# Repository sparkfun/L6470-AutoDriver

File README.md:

SparkFun AutoDriver - Stepper Motor Driver
==========================================

[*AutoDriver (BOB-13752)*](https://www.sparkfun.com/products/13752)

The AutoDriver is a bipolar stepper driver based on the ST Micro L6470 chip. It allows a processor to control a single 3A bipolar stepper motor across an 8-45V supply range.

Repository Contents
-------------------
* **/Hardware** - All Eagle design files (.brd, .sch)
* **/Libraries** - All Arduino libraries and board examples
* **/Production** - Test bed files and production panel files

Documentation
--------------
* **[Library](https://github.com/sparkfun/SparkFun_AutoDriver_Arduino_Library)** - Arduino library for the AutoDriver.
* **[Hookup Guide](https://learn.sparkfun.com/tutorials/getting-started-with-the-autodriver---v13)** - Basic hookup guide for the Auto Driver.
* **[SparkFun Fritzing repo](https://github.com/sparkfun/Fritzing_Parts)** - Fritzing diagrams for SparkFun products.
* **[SparkFun 3D Model repo](https://github.com/sparkfun/3D_Models)** - 3D models of SparkFun products. 
* **[SparkFun Graphical Datasheets](https://github.com/sparkfun/Graphical_Datasheets)** -Graphical Datasheets for various SparkFun products.

License Information
-------------------

This product is _**open source**_! 

Please review the LICENSE.md file for license information. 

If you have any questions or concerns on licensing, please contact techsupport@sparkfun.com.

Distributed as-is; no warranty is given.

- Your friends at SparkFun.

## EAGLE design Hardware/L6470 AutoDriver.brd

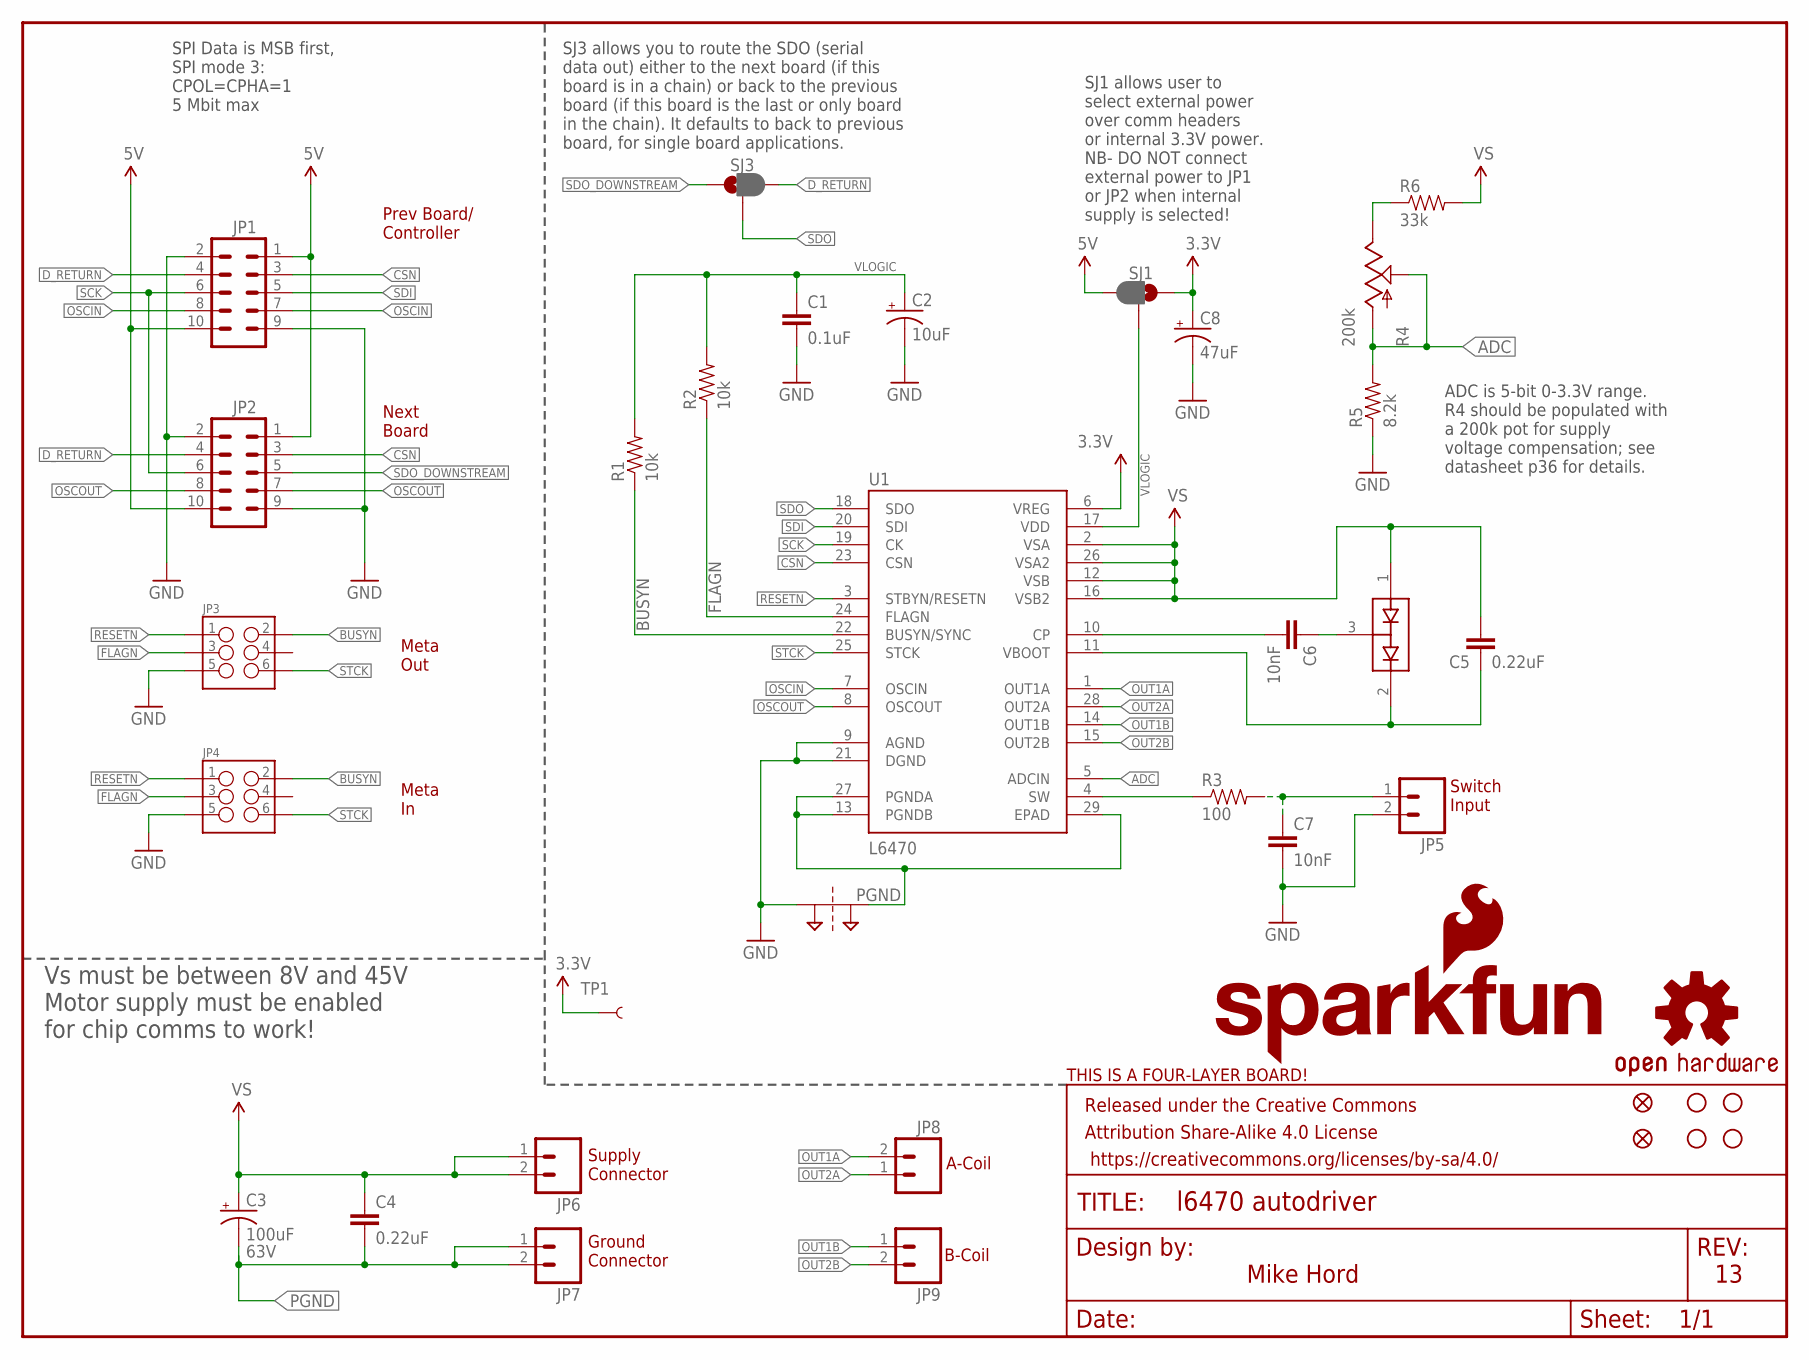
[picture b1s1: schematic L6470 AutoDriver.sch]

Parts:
C1: 0.1uF; 0603-CAP
C2: 10uF; EIA3216
C3: 100uF; NIC_10X10.5_CAP
C4, C5: 0.22uF; 0603-CAP
C6, C7: 10nF; 0603-CAP
C8: 47uF; EIA3528
D1: BAV99; SOT23-3
FID1, FID2: FIDUCIALUFIDUCIAL; MICRO-FIDUCIAL
FRAME1: FRAME-LETTER; CREATIVE_COMMONS
JP1, JP2: M05X2SHD; 2X5-SHROUDED
JP3, JP4: M03X2SHROUD; 2X3-SHROUDED
JP5, JP6, JP7, JP8, JP9: M023.5MM; SCREWTERMINAL-3.5MM-2
LOGO1: OSHW-LOGOM; OSHW-LOGO-M
LOGO2: SFE_LOGO_NAME_FLAME.2_INCH; SFE_LOGO_NAME_FLAME_.2
R1, R2: 10k; 0603-RES
R3: 100; 0603-RES
R4: 200k; 3362U
R5: 8.2k; 0603-RES
R6: 33k; 0603-RES
SJ1, SJ3: JUMPER-PAD-3-2OF3_NC_BY_PASTE; PAD-JUMPER-3-2OF3_NC_BY_PASTE_YES_SILK_FULL_BOX
SJ2: 2PT_GND_TIE
STANDOFF1, STANDOFF2, STANDOFF3, STANDOFF4: STAND-OFF
TP1: TEST-POINTTP_15TH_THRU; TP_15TH
U1: L6470; HTSSOP28
U$4: FOUR_LAYER_WARNING

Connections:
3.3V: C8.A (+), SJ1.1, TP1.P$1, U1.6 (VREG)
5V: JP1.1, JP1.10, JP2.1, JP2.10, SJ1.3
ADC: R4.P$2 (S), R4.P$3 (A), R5.2, U1.5 (ADCIN)
BUSYN: JP3.2, JP4.2, R1.1, U1.22 (BUSYN/SYNC)
CP_HIGH: C6.1, D1.3 (COM)
CSN: JP1.3, JP2.3, U1.23 (CSN)
D_RETURN: JP1.4, JP2.4, SJ3.3
FLAGN: JP3.3, JP4.3, R2.1, U1.24 (FLAGN)
GND: C1.2, C2.C (-), C7.2, C8.C (-), JP1.2, JP1.9, JP2.2, JP2.9, JP3.5, JP4.5, JP5.2, R5.1, SJ2.P$1, U1.9 (AGND), U1.21 (DGND)
unnamed: R4.P$1 (E), R6.1
OSCIN: JP1.7, JP1.8, U1.7 (OSCIN)
OSCOUT: JP2.7, JP2.8, U1.8 (OSCOUT)
OUT1A: JP8.2, U1.1 (OUT1A)
OUT1B: JP9.1, U1.14 (OUT1B)
OUT2A: JP8.1, U1.28 (OUT2A)
OUT2B: JP9.2, U1.15 (OUT2B)
PGND: C3.-, C4.2, JP7.1, JP7.2, SJ2.P$2, U1.13 (PGNDB), U1.27 (PGNDA), U1.29 (EPAD)
RESETN: JP3.1, JP4.1, U1.3 (STBYN/RESETN)
SCK: JP1.6, JP2.6, U1.19 (CK)
SDI: JP1.5, U1.20 (SDI)
SDO: SJ3.2, U1.18 (SDO)
SDO_DOWNSTREAM: JP2.5, SJ3.1
STCK: JP3.6, JP4.6, U1.25 (STCK)
SWITCH_INPUT: C7.1, JP5.1, R3.2
SWITCH_SIG: R3.1, U1.4 (SW)
VLOGIC: C1.1, C2.A (+), R1.2, R2.2, SJ1.2, U1.17 (VDD)
VS: C3.+, C4.1, C5.2, D1.1 (A1), JP6.1, JP6.2, R6.2, U1.2 (VSA), U1.12 (VSB), U1.16 (VSB2), U1.26 (VSA2)
V_BOOT: C5.1, D1.2 (C2), U1.11 (VBOOT)
V_CP: C6.2, U1.10 (CP)

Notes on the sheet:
63V
Switch Input
B-Coil
A-Coil
Supply Connector
Ground Connector
SJ1 allows user to select external power over comm headers or internal 3.3V power. NB- DO NOT connect external power to JP1 or JP2 when internal supply is selected!
Next Board
Prev Board/ Controller
Meta Out
Meta In
ADC is 5-bit 0-3.3V range. R4 should be populated with a 200k pot for supply voltage compensation; see datasheet p36 for details.
SPI Data is MSB first, SPI mode 3: CPOL=CPHA=1 5 Mbit max
Mike Hord
Vs must be between 8V and 45V Motor supply must be enabled for chip comms to work!
SJ3 allows you to route the SDO (serial data out) either to the next board (if this board is in a chain) or back to the previous board (if this board is the last or only board in the chain). It defaults to back to previous board, for single board applications.

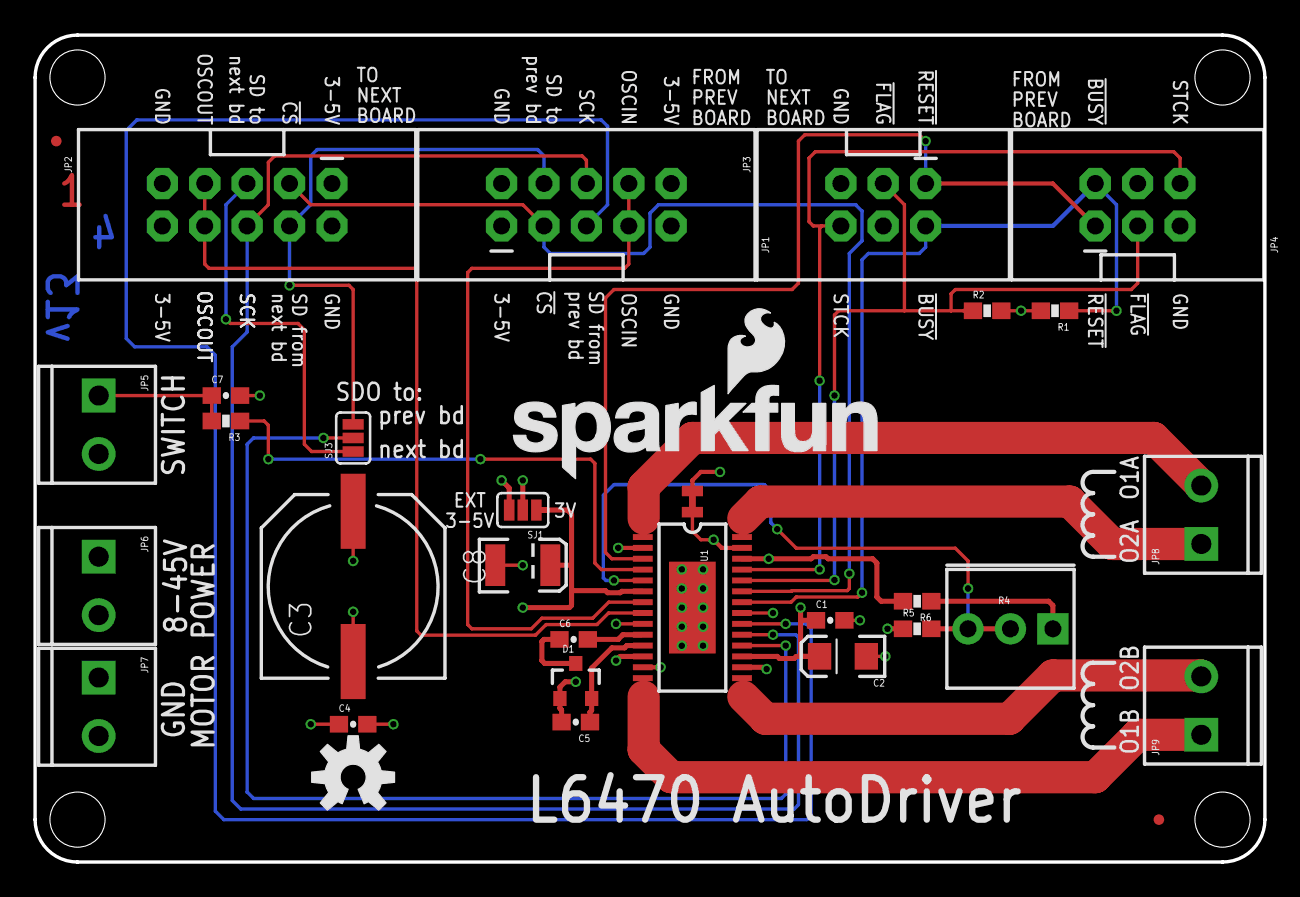
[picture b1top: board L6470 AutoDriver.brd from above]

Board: 4 copper layers, 73.7 x 49.5 mm, 39 parts (0 on the bottom side), 29 nets.

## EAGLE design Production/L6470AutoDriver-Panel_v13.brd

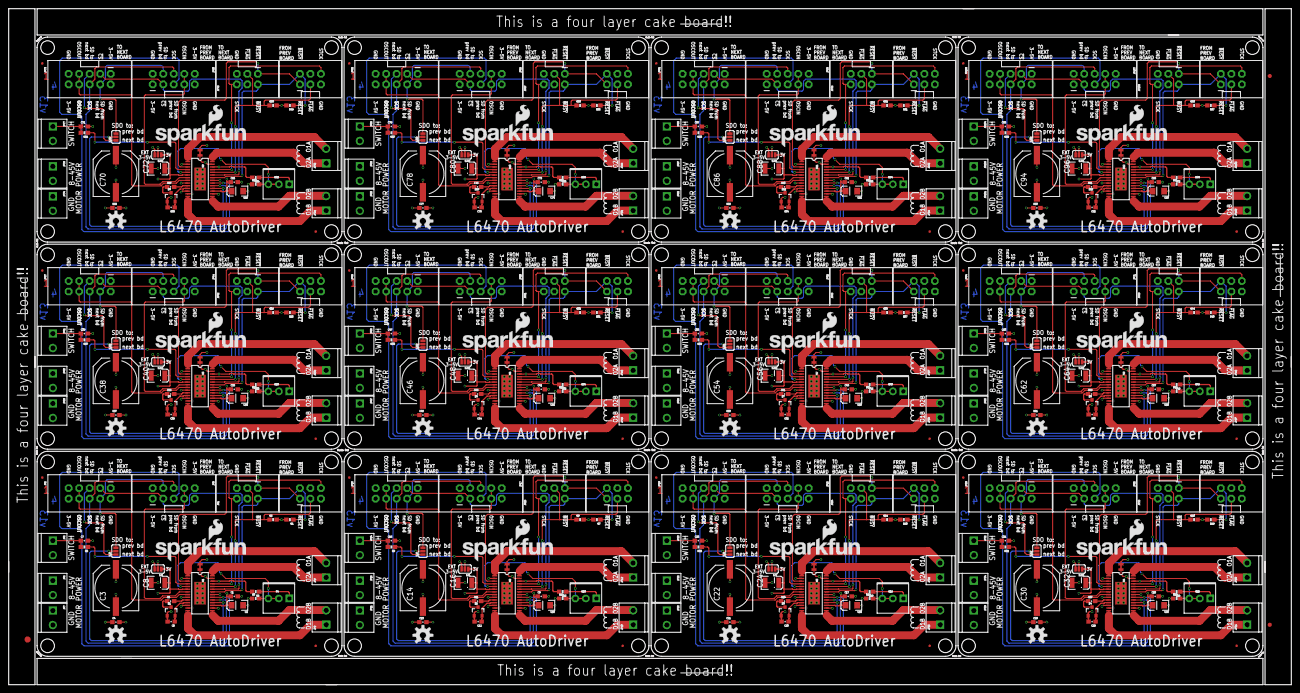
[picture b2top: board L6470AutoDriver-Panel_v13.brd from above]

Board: 4 copper layers, 309.9 x 163.3 mm, 447 parts (0 on the bottom side), 348 nets.

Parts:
C1, C9, C17, C25, C33, C41, C49, C57, C65, C73, C81, C89: 0.1uF; 0603-CAP
C2, C10, C18, C26, C34, C42, C50, C58, C66, C74, C82, C90: 10uF; EIA3216
C3, C14, C22, C30, C38, C46, C54, C62, C70, C78, C86, C94: 100uF; NIC_10X10.5_CAP
C4, C5, C12, C13, C20, C21, C28, C29, C36, C37, C44, C45, C52, C53, C60, C61, C68, C69, C76, C77, C84, C85, C92, C93: 0.22uF; 0603-CAP
C6, C7, C11, C15, C19, C23, C27, C31, C35, C39, C43, C47, C51, C55, C59, C63, C67, C71, C75, C79, C83, C87, C91, C95: 10nF; 0603-CAP
C8, C16, C24, C32, C40, C48, C56, C64, C72, C80, C88, C96: 47uF; EIA3528
D1, D2, D3, D4, D5, D6, D7, D8, D9, D10, D11, D12: BAV99; SOT23-3
E$1: FIDUCIAL-1.5X3
E$5, E$6: FIDUCIAL-1X2
FID1, FID2, FID3, FID4, FID5, FID6, FID7, FID8, FID9, FID10, FID11, FID12, FID13, FID14, FID15, FID16, FID17, FID18, FID19, FID20, FID21, FID22, FID23, FID24: FIDUCIALUFIDUCIAL; MICRO-FIDUCIAL
JP1, JP2, JP10, JP15, JP19, JP24, JP28, JP33, JP37, JP42, JP46, JP51, JP55, JP60, JP64, JP69, JP73, JP78, JP82, JP87, JP91, JP96, JP100, JP105: M05X2SHD; 2X5-SHROUDED
JP3, JP4, JP17, JP18, JP26, JP27, JP35, JP36, JP44, JP45, JP53, JP54, JP62, JP63, JP71, JP72, JP80, JP81, JP89, JP90, JP98, JP99, JP107, JP108: 2X3-SHROUDED
JP5, JP6, JP7, JP8, JP9, JP11, JP12, JP13, JP14, JP16, JP20, JP21, JP22, JP23, JP25, JP29, JP30, JP31, JP32, JP34, JP38, JP39, JP40, JP41, JP43, JP47, JP48, JP49, JP50, JP52, JP56, JP57, JP58, JP59, JP61, JP65, JP66, JP67, JP68, JP70, JP74, JP75, JP76, JP77, JP79, JP83, JP84, JP85, JP86, JP88, JP92, JP93, JP94, JP95, JP97, JP101, JP102, JP103, JP104, JP106: SCREWTERMINAL-3.5MM-2
LOGO1, LOGO3, LOGO5, LOGO7, LOGO9, LOGO11, LOGO13, LOGO15, LOGO17, LOGO19, LOGO21, LOGO23: OSHW-LOGOM; OSHW-LOGO-M
LOGO2, LOGO4, LOGO6, LOGO8, LOGO10, LOGO12, LOGO14, LOGO16, LOGO18, LOGO20, LOGO22, LOGO24: SFE_LOGO_NAME_FLAME.2_INCH; SFE_LOGO_NAME_FLAME_.2
R1, R2, R7, R8, R13, R14, R19, R20, R25, R26, R31, R32, R37, R38, R43, R44, R49, R50, R55, R56, R61, R62, R67, R68: 10k; 0603-RES
R3, R9, R15, R21, R27, R33, R39, R45, R51, R57, R63, R69: 100; 0603-RES
R4, R10, R16, R22, R28, R34, R40, R46, R52, R58, R64, R70: 200k; 3362U
R5, R11, R17, R23, R29, R35, R41, R47, R53, R59, R65, R71: 8.2k; 0603-RES
R6, R12, R18, R24, R30, R36, R42, R48, R54, R60, R66, R72: 33k; 0603-RES
SJ1, SJ3, SJ4, SJ6, SJ7, SJ9, SJ10, SJ12, SJ13, SJ15, SJ16, SJ18, SJ19, SJ21, SJ22, SJ24, SJ25, SJ27, SJ28, SJ30, SJ31, SJ33, SJ34, SJ36: JUMPER-PAD-3-2OF3_NC_BY_PASTE; PAD-JUMPER-3-2OF3_NC_BY_PASTE_YES_SILK_FULL_BOX
SJ2, SJ5, SJ8, SJ11, SJ14, SJ17, SJ20, SJ23, SJ26, SJ29, SJ32, SJ35: 2PT_GND_TIE
STANDOFF1, STANDOFF2, STANDOFF3, STANDOFF4, STANDOFF5, STANDOFF6, STANDOFF7, STANDOFF8, STANDOFF9, STANDOFF10, STANDOFF11, STANDOFF12, STANDOFF13, STANDOFF14, STANDOFF15, STANDOFF16, STANDOFF17, STANDOFF18, STANDOFF19, STANDOFF20, STANDOFF21, STANDOFF22, STANDOFF23, STANDOFF24, STANDOFF25, STANDOFF26, STANDOFF27, STANDOFF28, STANDOFF29, STANDOFF30, STANDOFF31, STANDOFF32, STANDOFF33, STANDOFF34, STANDOFF35, STANDOFF36, STANDOFF37, STANDOFF38, STANDOFF39, STANDOFF40, STANDOFF41, STANDOFF42, STANDOFF43, STANDOFF44, STANDOFF45, STANDOFF46, STANDOFF47, STANDOFF48: STAND-OFF
TP1, TP2, TP3, TP4, TP5, TP6, TP7, TP8, TP9, TP10, TP11, TP12: TEST-POINTTP_15TH_THRU; TP_15TH
U1, U2, U3, U4, U5, U6, U7, U8, U9, U10, U11, U12: L6470; HTSSOP28

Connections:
3.3V: C8.A, SJ1.1, TP1.P$1, U1.6
3.3V1: C16.A, SJ4.1, TP2.P$1, U2.6
3.3V2: C24.A, SJ7.1, TP3.P$1, U3.6
3.3V3: C32.A, SJ10.1, TP4.P$1, U4.6
3.3V4: C40.A, SJ13.1, TP5.P$1, U5.6
3.3V5: C48.A, SJ16.1, TP6.P$1, U6.6
3.3V6: C56.A, SJ19.1, TP7.P$1, U7.6
3.3V7: C64.A, SJ22.1, TP8.P$1, U8.6
3.3V8: C72.A, SJ25.1, TP9.P$1, U9.6
3.3V9: C80.A, SJ28.1, TP10.P$1, U10.6
3.3V10: C88.A, SJ31.1, TP11.P$1, U11.6
3.3V11: C96.A, SJ34.1, TP12.P$1, U12.6
5V: JP1.1, JP1.10, JP2.1, JP2.10, SJ1.3
5V1: JP10.1, JP10.10, JP15.1, JP15.10, SJ4.3
5V2: JP19.1, JP19.10, JP24.1, JP24.10, SJ7.3
5V3: JP28.1, JP28.10, JP33.1, JP33.10, SJ10.3
5V4: JP37.1, JP37.10, JP42.1, JP42.10, SJ13.3
5V5: JP46.1, JP46.10, JP51.1, JP51.10, SJ16.3
5V6: JP55.1, JP55.10, JP60.1, JP60.10, SJ19.3
5V7: JP64.1, JP64.10, JP69.1, JP69.10, SJ22.3
5V8: JP73.1, JP73.10, JP78.1, JP78.10, SJ25.3
5V9: JP82.1, JP82.10, JP87.1, JP87.10, SJ28.3
5V10: JP91.1, JP91.10, JP96.1, JP96.10, SJ31.3
5V11: JP100.1, JP100.10, JP105.1, JP105.10, SJ34.3
ADC: R4.P$2, R4.P$3, R5.2, U1.5
ADC1: R10.P$2, R10.P$3, R11.2, U2.5
ADC2: R16.P$2, R16.P$3, R17.2, U3.5
ADC3: R22.P$2, R22.P$3, R23.2, U4.5
ADC4: R28.P$2, R28.P$3, R29.2, U5.5
ADC5: R34.P$2, R34.P$3, R35.2, U6.5
ADC6: R40.P$2, R40.P$3, R41.2, U7.5
ADC7: R46.P$2, R46.P$3, R47.2, U8.5
ADC8: R52.P$2, R52.P$3, R53.2, U9.5
ADC9: R58.P$2, R58.P$3, R59.2, U10.5
ADC10: R64.P$2, R64.P$3, R65.2, U11.5
ADC11: R70.P$2, R70.P$3, R71.2, U12.5
BUSYN: JP3.2, JP4.2, R1.1, U1.22
BUSYN1: JP17.2, JP18.2, R7.1, U2.22
BUSYN2: JP26.2, JP27.2, R13.1, U3.22
BUSYN3: JP35.2, JP36.2, R19.1, U4.22
BUSYN4: JP44.2, JP45.2, R25.1, U5.22
BUSYN5: JP53.2, JP54.2, R31.1, U6.22
BUSYN6: JP62.2, JP63.2, R37.1, U7.22
BUSYN7: JP71.2, JP72.2, R43.1, U8.22
BUSYN8: JP80.2, JP81.2, R49.1, U9.22
BUSYN9: JP89.2, JP90.2, R55.1, U10.22
BUSYN10: JP98.2, JP99.2, R61.1, U11.22
BUSYN11: JP107.2, JP108.2, R67.1, U12.22
CP_HIGH: C6.1, D1.3
CP_HIGH1: C11.1, D2.3
CP_HIGH2: C19.1, D3.3
CP_HIGH3: C27.1, D4.3
CP_HIGH4: C35.1, D5.3
CP_HIGH5: C43.1, D6.3
CP_HIGH6: C51.1, D7.3
CP_HIGH7: C59.1, D8.3
CP_HIGH8: C67.1, D9.3
CP_HIGH9: C75.1, D10.3
CP_HIGH10: C83.1, D11.3
CP_HIGH11: C91.1, D12.3
CSN: JP1.3, JP2.3, U1.23
CSN1: JP10.3, JP15.3, U2.23
CSN2: JP19.3, JP24.3, U3.23
CSN3: JP28.3, JP33.3, U4.23
CSN4: JP37.3, JP42.3, U5.23
CSN5: JP46.3, JP51.3, U6.23
CSN6: JP55.3, JP60.3, U7.23
CSN7: JP64.3, JP69.3, U8.23
CSN8: JP73.3, JP78.3, U9.23
CSN9: JP82.3, JP87.3, U10.23
CSN10: JP91.3, JP96.3, U11.23
CSN11: JP100.3, JP105.3, U12.23
D_RETURN: JP1.4, JP2.4, SJ3.3
D_RETURN1: JP10.4, JP15.4, SJ6.3
D_RETURN2: JP19.4, JP24.4, SJ9.3
D_RETURN3: JP28.4, JP33.4, SJ12.3
D_RETURN4: JP37.4, JP42.4, SJ15.3
D_RETURN5: JP46.4, JP51.4, SJ18.3
D_RETURN6: JP55.4, JP60.4, SJ21.3
D_RETURN7: JP64.4, JP69.4, SJ24.3
D_RETURN8: JP73.4, JP78.4, SJ27.3
D_RETURN9: JP82.4, JP87.4, SJ30.3
D_RETURN10: JP91.4, JP96.4, SJ33.3
D_RETURN11: JP100.4, JP105.4, SJ36.3
FLAGN: JP3.3, JP4.3, R2.1, U1.24
FLAGN1: JP17.3, JP18.3, R8.1, U2.24
FLAGN2: JP26.3, JP27.3, R14.1, U3.24
FLAGN3: JP35.3, JP36.3, R20.1, U4.24
FLAGN4: JP44.3, JP45.3, R26.1, U5.24
FLAGN5: JP53.3, JP54.3, R32.1, U6.24
FLAGN6: JP62.3, JP63.3, R38.1, U7.24
FLAGN7: JP71.3, JP72.3, R44.1, U8.24
FLAGN8: JP80.3, JP81.3, R50.1, U9.24
FLAGN9: JP89.3, JP90.3, R56.1, U10.24
FLAGN10: JP98.3, JP99.3, R62.1, U11.24
FLAGN11: JP107.3, JP108.3, R68.1, U12.24
GND: C1.2, C2.C, C7.2, C8.C, JP1.2, JP1.9, JP2.2, JP2.9, JP3.5, JP4.5, JP5.2, R5.1, SJ2.P$1, U1.9, U1.21
GND1: C9.2, C10.C, C15.2, C16.C, JP10.2, JP10.9, JP14.2, JP15.2, JP15.9, JP17.5, JP18.5, R11.1, SJ5.P$1, U2.9, U2.21
GND2: C17.2, C18.C, C23.2, C24.C, JP19.2, JP19.9, JP23.2, JP24.2, JP24.9, JP26.5, JP27.5, R17.1, SJ8.P$1, U3.9, U3.21
GND3: C25.2, C26.C, C31.2, C32.C, JP28.2, JP28.9, JP32.2, JP33.2, JP33.9, JP35.5, JP36.5, R23.1, SJ11.P$1, U4.9, U4.21
GND4: C33.2, C34.C, C39.2, C40.C, JP37.2, JP37.9, JP41.2, JP42.2, JP42.9, JP44.5, JP45.5, R29.1, SJ14.P$1, U5.9, U5.21
GND5: C41.2, C42.C, C47.2, C48.C, JP46.2, JP46.9, JP50.2, JP51.2, JP51.9, JP53.5, JP54.5, R35.1, SJ17.P$1, U6.9, U6.21
GND6: C49.2, C50.C, C55.2, C56.C, JP55.2, JP55.9, JP59.2, JP60.2, JP60.9, JP62.5, JP63.5, R41.1, SJ20.P$1, U7.9, U7.21
GND7: C57.2, C58.C, C63.2, C64.C, JP64.2, JP64.9, JP68.2, JP69.2, JP69.9, JP71.5, JP72.5, R47.1, SJ23.P$1, U8.9, U8.21
GND8: C65.2, C66.C, C71.2, C72.C, JP73.2, JP73.9, JP77.2, JP78.2, JP78.9, JP80.5, JP81.5, R53.1, SJ26.P$1, U9.9, U9.21
GND9: C73.2, C74.C, C79.2, C80.C, JP82.2, JP82.9, JP86.2, JP87.2, JP87.9, JP89.5, JP90.5, R59.1, SJ29.P$1, U10.9, U10.21
GND10: C81.2, C82.C, C87.2, C88.C, JP91.2, JP91.9, JP95.2, JP96.2, JP96.9, JP98.5, JP99.5, R65.1, SJ32.P$1, U11.9, U11.21
GND11: C89.2, C90.C, C95.2, C96.C, JP100.2, JP100.9, JP104.2, JP105.2, JP105.9, JP107.5, JP108.5, R71.1, SJ35.P$1, U12.9, U12.21
unnamed: R10.P$1, R12.1
unnamed: R16.P$1, R18.1
unnamed: R22.P$1, R24.1
unnamed: R28.P$1, R30.1
unnamed: R34.P$1, R36.1
unnamed: R40.P$1, R42.1
unnamed: R46.P$1, R48.1
unnamed: R52.P$1, R54.1
unnamed: R58.P$1, R60.1
unnamed: R64.P$1, R66.1
unnamed: R4.P$1, R6.1
unnamed: R70.P$1, R72.1
OSCIN: JP1.7, JP1.8, U1.7
OSCIN1: JP15.7, JP15.8, U2.7
OSCIN2: JP24.7, JP24.8, U3.7
OSCIN3: JP33.7, JP33.8, U4.7
OSCIN4: JP42.7, JP42.8, U5.7
OSCIN5: JP51.7, JP51.8, U6.7
OSCIN6: JP60.7, JP60.8, U7.7
OSCIN7: JP69.7, JP69.8, U8.7
OSCIN8: JP78.7, JP78.8, U9.7
OSCIN9: JP87.7, JP87.8, U10.7
OSCIN10: JP96.7, JP96.8, U11.7
OSCIN11: JP105.7, JP105.8, U12.7
OSCOUT: JP2.7, JP2.8, U1.8
OSCOUT1: JP10.7, JP10.8, U2.8
OSCOUT2: JP19.7, JP19.8, U3.8
OSCOUT3: JP28.7, JP28.8, U4.8
OSCOUT4: JP37.7, JP37.8, U5.8
OSCOUT5: JP46.7, JP46.8, U6.8
OSCOUT6: JP55.7, JP55.8, U7.8
OSCOUT7: JP64.7, JP64.8, U8.8
OSCOUT8: JP73.7, JP73.8, U9.8
OSCOUT9: JP82.7, JP82.8, U10.8
OSCOUT10: JP91.7, JP91.8, U11.8
OSCOUT11: JP100.7, JP100.8, U12.8
OUT1A: JP8.2, U1.1
OUT1A1: JP12.2, U2.1
OUT1A2: JP21.2, U3.1
OUT1A3: JP30.2, U4.1
OUT1A4: JP39.2, U5.1
OUT1A5: JP48.2, U6.1
OUT1A6: JP57.2, U7.1
OUT1A7: JP66.2, U8.1
OUT1A8: JP75.2, U9.1
OUT1A9: JP84.2, U10.1
OUT1A10: JP93.2, U11.1
OUT1A11: JP102.2, U12.1
OUT1B: JP9.1, U1.14
OUT1B1: JP13.1, U2.14
OUT1B2: JP22.1, U3.14
OUT1B3: JP31.1, U4.14
OUT1B4: JP40.1, U5.14
OUT1B5: JP49.1, U6.14
OUT1B6: JP58.1, U7.14
OUT1B7: JP67.1, U8.14
OUT1B8: JP76.1, U9.14
OUT1B9: JP85.1, U10.14
OUT1B10: JP94.1, U11.14
OUT1B11: JP103.1, U12.14
OUT2A: JP8.1, U1.28
OUT2A1: JP12.1, U2.28
OUT2A2: JP21.1, U3.28
OUT2A3: JP30.1, U4.28
OUT2A4: JP39.1, U5.28
OUT2A5: JP48.1, U6.28
OUT2A6: JP57.1, U7.28
OUT2A7: JP66.1, U8.28
OUT2A8: JP75.1, U9.28
OUT2A9: JP84.1, U10.28
OUT2A10: JP93.1, U11.28
OUT2A11: JP102.1, U12.28
OUT2B: JP9.2, U1.15
OUT2B1: JP13.2, U2.15
OUT2B2: JP22.2, U3.15
OUT2B3: JP31.2, U4.15
OUT2B4: JP40.2, U5.15
OUT2B5: JP49.2, U6.15
OUT2B6: JP58.2, U7.15
OUT2B7: JP67.2, U8.15
OUT2B8: JP76.2, U9.15
OUT2B9: JP85.2, U10.15
OUT2B10: JP94.2, U11.15
OUT2B11: JP103.2, U12.15
PGND: C3.-, C4.2, JP7.1, JP7.2, SJ2.P$2, U1.13, U1.27, U1.29
PGND1: C13.2, C14.-, JP11.1, JP11.2, SJ5.P$2, U2.13, U2.27, U2.29
PGND2: C21.2, C22.-, JP20.1, JP20.2, SJ8.P$2, U3.13, U3.27, U3.29
PGND3: C29.2, C30.-, JP29.1, JP29.2, SJ11.P$2, U4.13, U4.27, U4.29
PGND4: C37.2, C38.-, JP38.1, JP38.2, SJ14.P$2, U5.13, U5.27, U5.29
PGND5: C45.2, C46.-, JP47.1, JP47.2, SJ17.P$2, U6.13, U6.27, U6.29
PGND6: C53.2, C54.-, JP56.1, JP56.2, SJ20.P$2, U7.13, U7.27, U7.29
PGND7: C61.2, C62.-, JP65.1, JP65.2, SJ23.P$2, U8.13, U8.27, U8.29
PGND8: C69.2, C70.-, JP74.1, JP74.2, SJ26.P$2, U9.13, U9.27, U9.29
PGND9: C77.2, C78.-, JP83.1, JP83.2, SJ29.P$2, U10.13, U10.27, U10.29
PGND10: C85.2, C86.-, JP92.1, JP92.2, SJ32.P$2, U11.13, U11.27, U11.29
PGND11: C93.2, C94.-, JP101.1, JP101.2, SJ35.P$2, U12.13, U12.27, U12.29
RESETN: JP3.1, JP4.1, U1.3
RESETN1: JP17.1, JP18.1, U2.3
RESETN2: JP26.1, JP27.1, U3.3
RESETN3: JP35.1, JP36.1, U4.3
RESETN4: JP44.1, JP45.1, U5.3
RESETN5: JP53.1, JP54.1, U6.3
RESETN6: JP62.1, JP63.1, U7.3
RESETN7: JP71.1, JP72.1, U8.3
RESETN8: JP80.1, JP81.1, U9.3
RESETN9: JP89.1, JP90.1, U10.3
RESETN10: JP98.1, JP99.1, U11.3
RESETN11: JP107.1, JP108.1, U12.3
SCK: JP1.6, JP2.6, U1.19
SCK1: JP10.6, JP15.6, U2.19
SCK2: JP19.6, JP24.6, U3.19
SCK3: JP28.6, JP33.6, U4.19
SCK4: JP37.6, JP42.6, U5.19
SCK5: JP46.6, JP51.6, U6.19
SCK6: JP55.6, JP60.6, U7.19
SCK7: JP64.6, JP69.6, U8.19
SCK8: JP73.6, JP78.6, U9.19
SCK9: JP82.6, JP87.6, U10.19
SCK10: JP91.6, JP96.6, U11.19
SCK11: JP100.6, JP105.6, U12.19
SDI: JP1.5, U1.20
SDI1: JP15.5, U2.20
SDI2: JP24.5, U3.20
SDI3: JP33.5, U4.20
SDI4: JP42.5, U5.20
SDI5: JP51.5, U6.20
SDI6: JP60.5, U7.20
SDI7: JP69.5, U8.20
SDI8: JP78.5, U9.20
SDI9: JP87.5, U10.20
SDI10: JP96.5, U11.20
SDI11: JP105.5, U12.20
SDO: SJ3.2, U1.18
SDO1: SJ6.2, U2.18
SDO2: SJ9.2, U3.18
SDO3: SJ12.2, U4.18
SDO4: SJ15.2, U5.18
SDO5: SJ18.2, U6.18
SDO6: SJ21.2, U7.18
SDO7: SJ24.2, U8.18
SDO8: SJ27.2, U9.18
SDO9: SJ30.2, U10.18
SDO10: SJ33.2, U11.18
SDO11: SJ36.2, U12.18
SDO_DOWNSTREAM: JP2.5, SJ3.1
SDO_DOWNSTREAM1: JP10.5, SJ6.1
SDO_DOWNSTREAM2: JP19.5, SJ9.1
SDO_DOWNSTREAM3: JP28.5, SJ12.1
SDO_DOWNSTREAM4: JP37.5, SJ15.1
SDO_DOWNSTREAM5: JP46.5, SJ18.1
SDO_DOWNSTREAM6: JP55.5, SJ21.1
SDO_DOWNSTREAM7: JP64.5, SJ24.1
SDO_DOWNSTREAM8: JP73.5, SJ27.1
SDO_DOWNSTREAM9: JP82.5, SJ30.1
SDO_DOWNSTREAM10: JP91.5, SJ33.1
SDO_DOWNSTREAM11: JP100.5, SJ36.1
STCK: JP3.6, JP4.6, U1.25
STCK1: JP17.6, JP18.6, U2.25
STCK2: JP26.6, JP27.6, U3.25
STCK3: JP35.6, JP36.6, U4.25
STCK4: JP44.6, JP45.6, U5.25
STCK5: JP53.6, JP54.6, U6.25
STCK6: JP62.6, JP63.6, U7.25
STCK7: JP71.6, JP72.6, U8.25
STCK8: JP80.6, JP81.6, U9.25
STCK9: JP89.6, JP90.6, U10.25
STCK10: JP98.6, JP99.6, U11.25
STCK11: JP107.6, JP108.6, U12.25
SWITCH_INPUT: C7.1, JP5.1, R3.2
SWITCH_INPUT1: C15.1, JP14.1, R9.2
SWITCH_INPUT2: C23.1, JP23.1, R15.2
SWITCH_INPUT3: C31.1, JP32.1, R21.2
SWITCH_INPUT4: C39.1, JP41.1, R27.2
SWITCH_INPUT5: C47.1, JP50.1, R33.2
SWITCH_INPUT6: C55.1, JP59.1, R39.2
SWITCH_INPUT7: C63.1, JP68.1, R45.2
SWITCH_INPUT8: C71.1, JP77.1, R51.2
SWITCH_INPUT9: C79.1, JP86.1, R57.2
SWITCH_INPUT10: C87.1, JP95.1, R63.2
SWITCH_INPUT11: C95.1, JP104.1, R69.2
SWITCH_SIG: R3.1, U1.4
SWITCH_SIG1: R9.1, U2.4
SWITCH_SIG2: R15.1, U3.4
SWITCH_SIG3: R21.1, U4.4
SWITCH_SIG4: R27.1, U5.4
SWITCH_SIG5: R33.1, U6.4
SWITCH_SIG6: R39.1, U7.4
SWITCH_SIG7: R45.1, U8.4
SWITCH_SIG8: R51.1, U9.4
SWITCH_SIG9: R57.1, U10.4
SWITCH_SIG10: R63.1, U11.4
SWITCH_SIG11: R69.1, U12.4
VLOGIC: C1.1, C2.A, R1.2, R2.2, SJ1.2, U1.17
VLOGIC1: C9.1, C10.A, R7.2, R8.2, SJ4.2, U2.17
VLOGIC2: C17.1, C18.A, R13.2, R14.2, SJ7.2, U3.17
VLOGIC3: C25.1, C26.A, R19.2, R20.2, SJ10.2, U4.17
VLOGIC4: C33.1, C34.A, R25.2, R26.2, SJ13.2, U5.17
VLOGIC5: C41.1, C42.A, R31.2, R32.2, SJ16.2, U6.17
VLOGIC6: C49.1, C50.A, R37.2, R38.2, SJ19.2, U7.17
VLOGIC7: C57.1, C58.A, R43.2, R44.2, SJ22.2, U8.17
VLOGIC8: C65.1, C66.A, R49.2, R50.2, SJ25.2, U9.17
VLOGIC9: C73.1, C74.A, R55.2, R56.2, SJ28.2, U10.17
VLOGIC10: C81.1, C82.A, R61.2, R62.2, SJ31.2, U11.17
VLOGIC11: C89.1, C90.A, R67.2, R68.2, SJ34.2, U12.17
VS: C3.+, C4.1, C5.2, D1.1, JP6.1, JP6.2, R6.2, U1.2, U1.12, U1.16, U1.26
VS1: C12.2, C13.1, C14.+, D2.1, JP16.1, JP16.2, R12.2, U2.2, U2.12, U2.16, U2.26
VS2: C20.2, C21.1, C22.+, D3.1, JP25.1, JP25.2, R18.2, U3.2, U3.12, U3.16, U3.26
VS3: C28.2, C29.1, C30.+, D4.1, JP34.1, JP34.2, R24.2, U4.2, U4.12, U4.16, U4.26
VS4: C36.2, C37.1, C38.+, D5.1, JP43.1, JP43.2, R30.2, U5.2, U5.12, U5.16, U5.26
VS5: C44.2, C45.1, C46.+, D6.1, JP52.1, JP52.2, R36.2, U6.2, U6.12, U6.16, U6.26
VS6: C52.2, C53.1, C54.+, D7.1, JP61.1, JP61.2, R42.2, U7.2, U7.12, U7.16, U7.26
VS7: C60.2, C61.1, C62.+, D8.1, JP70.1, JP70.2, R48.2, U8.2, U8.12, U8.16, U8.26
VS8: C68.2, C69.1, C70.+, D9.1, JP79.1, JP79.2, R54.2, U9.2, U9.12, U9.16, U9.26
VS9: C76.2, C77.1, C78.+, D10.1, JP88.1, JP88.2, R60.2, U10.2, U10.12, U10.16, U10.26
VS10: C84.2, C85.1, C86.+, D11.1, JP97.1, JP97.2, R66.2, U11.2, U11.12, U11.16, U11.26
VS11: C92.2, C93.1, C94.+, D12.1, JP106.1, JP106.2, R72.2, U12.2, U12.12, U12.16, U12.26
V_BOOT: C5.1, D1.2, U1.11
V_BOOT1: C12.1, D2.2, U2.11
V_BOOT2: C20.1, D3.2, U3.11
V_BOOT3: C28.1, D4.2, U4.11
V_BOOT4: C36.1, D5.2, U5.11
V_BOOT5: C44.1, D6.2, U6.11
V_BOOT6: C52.1, D7.2, U7.11
V_BOOT7: C60.1, D8.2, U8.11
V_BOOT8: C68.1, D9.2, U9.11
V_BOOT9: C76.1, D10.2, U10.11
V_BOOT10: C84.1, D11.2, U11.11
V_BOOT11: C92.1, D12.2, U12.11
V_CP: C6.2, U1.10
V_CP1: C11.2, U2.10
V_CP2: C19.2, U3.10
V_CP3: C27.2, U4.10
V_CP4: C35.2, U5.10
V_CP5: C43.2, U6.10
V_CP6: C51.2, U7.10
V_CP7: C59.2, U8.10
V_CP8: C67.2, U9.10
V_CP9: C75.2, U10.10
V_CP10: C83.2, U11.10
V_CP11: C91.2, U12.10

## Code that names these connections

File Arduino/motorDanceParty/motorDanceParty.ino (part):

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
#include "notes.h"

#define SS0              10  // Wire this to the CSN pin
#define SS1              9
#define SS2              8
#define MOSI             11  // Wire this to the SDI pin
#define MISO             12  // Wire this to the SDO pin
#define SCK              13  // Wire this to the CK pin
#define dSPIN_RESET      6   // Wire this to the STBY line
#define dSPIN_BUSYN      4   // Wire this to the BSYN line
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#define dSPIN_STEP_SEL_1_64  0x06
#define dSPIN_STEP_SEL_1_128 0x07

// ...next, define the SYNC_EN bit. When set, the BUSYN pin will instead
//  output a clock related to the full-step frequency as defined by the
//  SYNC_SEL bits below.
#define dSPIN_STEP_MODE_SYNC_EN	 0x80  // Mask for this bit
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
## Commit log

2012-11-09 Initial commit, before review.
2012-11-13 v01 files, as sent to protos.
    Mostly unchanged from initial commit; changed some part placements,
    some silk.
2012-12-05 Adding the example code I wrote for the original L6470 driver board.
    Going to be quite thoroughly rejiggered for the new board, mostly for stylistic purposes.
2012-12-11 Tidying up the example code some; that's still in process.
    This is to update the hardware files to v02- shrink the board
    a bit.
2012-12-18 Changes for v02- second proto round Shrank overall board size by about 15% Added a pad for extra chip select signal Improved text placement
2013-02-18 Fix mask on bottom layer
2013-06-19 Added four-layer warning to files.
2013-06-27 Updated for v10 redboard
2013-06-27 Add all files for v10, this time
2013-06-27 Production ready
    created 4 board panel; added fiducials
2013-07-08 Add library and library test sketch
2013-08-30 Adding README and fixing library structure
2013-11-04 Reduce from 3 to 2 boards in example sketch
2013-11-04 Update library to full release version - Change SPI mode - Add a few funcs (setMinSpeed, get/set mark, get/set pos) - Move setLoSpdOpt()
2013-11-05 Fix SPI mode, dSPINConstants.h file
2013-11-05 Fix SPI again. Gr.
2014-05-27 configStepMode update fixes microstepping
    variable name typo caused intended parameter never to be used.
    stepModeConfig |= (stepModeConfig&0x07);
    was probably meant to be
    stepModeConfig |= (stepMode&0x07);
2014-06-19 fixed: AutoDriver::configStepMode - param was not used
2014-06-24 Update dSPIN_example.ino
    Fixed the reset pin define so it matches the diagram in the tutorial.
2014-06-24 Update dSPIN_example.ino
    Undo the last change. That's not what I meant to fix.
2014-08-06 0603 update, Sch work, cap change
    Updated res/caps to 0603
    large cap updated to smaller silk/pad size
    jumper indicator added, OSHW logo upgraded
2014-10-02 Moved via
2014-10-07 Fixed bstop
2014-10-07 fixed b stop
2014-10-15 Connect CSN to CSN_OUT, minor fixes
2014-12-19 Making changes suggest by Pete L
2015-01-08 adding corresponding getters for setters in AutoDriverConfig
2015-01-09 fixing bugs: OC & VC get/set, and MIN_SPEED
    OC (over current) and VC (voltage compensation) masking was incorrect.
    Fixed masks for read and write.
    MIN_SPEED packets were only transferring 12 (not 13 bits). Fixed.
2015-01-09 adding example arduino sketch: GetSetParamTest.ino
    Gets and sets a bunch of parameters and checks that the same value
    returns.
2015-04-03 declaring all chars as signed + standard SPI calls
2015-04-03 Switching to standard SPI library calls
2015-04-30 Fixed more feedback from Pete after 1st proto cam failure
2015-05-04 Adjust file structure and add library readme
2015-05-04 Squashed 'Libraries/Arduino/' content from commit 72894eb
    git-subtree-dir: Libraries/Arduino
    git-subtree-split: 72894eb51289e93a6878a00568dc00134f6b6def
2015-05-04 Integrated library, library readme
2015-09-10 Significant changes from customer feedback: - now more daisy chainable - labels changed to make more sense - Change C5 to 220nF
2015-09-10 Changes from customer feedback: - now easier to daisy chain! - labels make more sense in light of daisy chaining - change C5 to 220nF
2015-09-15 Fix minor stuff from QC feedback
2016-06-28 Final file changes from revision
2016-06-30 Removed revised by from board
2016-07-01 created panel v12
2016-07-06 Fixed BSilk to match TSilk, advanced version number
2016-07-06 Fixed one more silk mistake
2016-07-07 created panel v13
2016-09-19 Updating git files, cleaning up README
2016-09-19 Squashed 'Libraries/Arduino/' changes from 72894eb..6ed7fd4
    6ed7fd4 Updating library properties version number
    a16b935 Updating hookup guide link
    21c0dcc Updating readme
    8d1e038 Fixed parameter transfer function
    beb4b9e Added in a couple of fixes from the community based on pull requests
    41d5bea Changes for v_13 of the hardware - supports multiple boards with one CS line - supports multiple SPI buses or a non-standard SPI bus
2016-09-19 merging library changes
2016-12-01 Squashed 'Libraries/Arduino/' changes from 6ed7fd4..38ad4dd
    38ad4dd Fixed ABSPOS overflow error
    git-subtree-dir: Libraries/Arduino
    git-subtree-split: 38ad4dd967539faa12b01ab82b326de3283b527b
2016-12-13 Squashed 'Libraries/Arduino/' changes from 38ad4dd..b0d59c0
    b0d59c0 Removed some debug printing
    3c951bd Fixed sign propagation issue
    git-subtree-dir: Libraries/Arduino
    git-subtree-split: b0d59c03c996b31586ec3b43881ccdcfdb33056c
2016-12-13 Update README with new SKU
2017-08-02 motor status fix
2025-06-27 Update README.md
    Updating link

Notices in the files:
parts and their libraries:
SparkFun-Resistors: Licensing: CC v3.0 Share-Alike You are welcome to use this library for commercial purposes.
SparkFun-Aesthetics: Released under the Creative Commons Attribution Share-Alike 4.0 License
SparkFun-Aesthetics: https://creativecommons.org/licenses/by-sa/4.0
